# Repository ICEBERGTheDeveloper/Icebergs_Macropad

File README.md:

# Icebergs' Macropad
This is the repo for my first macropad creation!

My macropad has 9 keyboard switches in a matrix, an OLED screen and a Rotary encoder! I will use it for video editing, gaming, and just other usefull things on my computer!
## CAD Model
The whole macropad fits together with just 4 screws on the case.

## Case
I designed this to just hold the PCB with no extra screws. I made 2 support columns underneath the PCB to hold it up at the right height, and it should fit snug with not much wiggle room.
Once I get the parts in real life, I can make the case better as I do not know the actual dimentions for the OLED screen.

## PCB
The PCB was designed with 9 switches, 9 diodes, the Seeed Studio XIAO RP2040, an EC11 Rotary encoder, a 128x32 OLED screen, and a nice silkscreen graphic! The mounting holes in it are for the future if I need to mount the PCB inside the case, but for now, I wont be using them :)

## The Schematic

## Software
The software was made with KMK.
I have most of the code complete, just need to change the buttons and OLED screen
- Currently the switches are just mapped to normal characters, when I get the macropad I will start thinking of what to map them to
### Here are some features I included:
- 3 keyboard layers (1 default, 1 gaming and 1 video editing) - As i said earlier, I only have them mapped to characters currently
- Encoder to switch the layer (double click encoder to enter 'layer switching mode' and then turn encoder clockwise to go to next layer, counter clockwise to go to previous layer, and click the encoder again to confirm)
- OLED screen - This currently only has some text... I will be editing this a lot when my macropad arrives
The software was probably my favourite part of making this macropad (along with PCB design)

## BOM
Finaly, all the parts I used.
- 9x Through-hole 1N4148 Diodes
- 9x MX-Style switches
- 1x EC11 Rotary encoder
- 1x 0.91 inch OLED display
- 9x Blank DSA keycaps
- 4x M3x16mm screws
- And I am *pretty* sure that the heatset inserts are needed... Please tell me? If they are: 4x M3x5mx4mm heatset inserts

#### I do not need the 3D printed case - I have a 3D printer at home

Thank you HackClub for giving us this awesome experience!

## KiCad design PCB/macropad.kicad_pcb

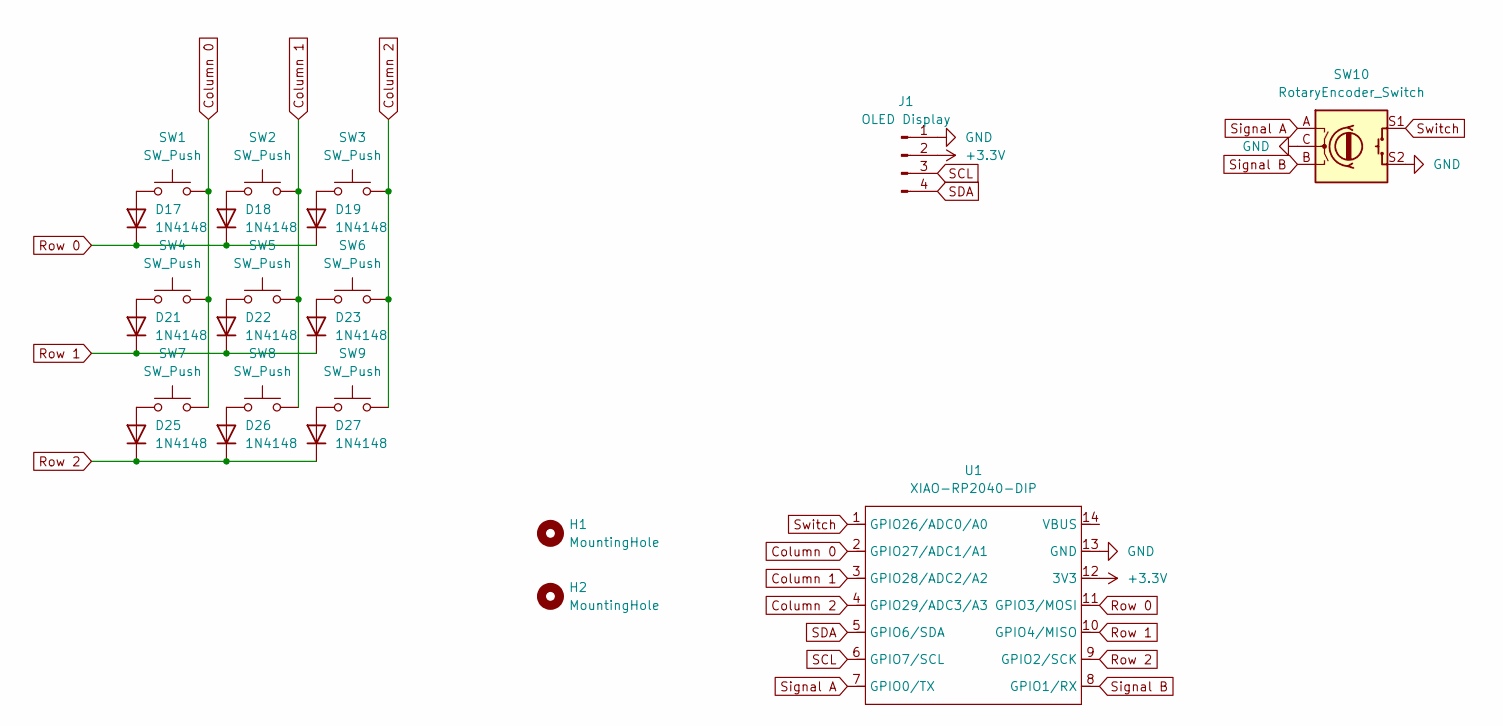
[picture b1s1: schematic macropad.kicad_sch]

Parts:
D17, D18, D19, D21, D22, D23, D25, D26, D27: 1N4148; D_DO-35_SOD27_P7.62mm_Horizontal
H1, H2: MountingHole; MountingHole_3.2mm_M3
J1: OLED Display; SSD1306-0.91-OLED-4pin-128x32
SW1, SW2, SW3, SW4, SW5, SW6, SW7, SW8, SW9: SW_Push; SW_Cherry_MX_1.00u_PCB
SW10: RotaryEncoder_Switch; RotaryEncoder_Alps_EC11E-Switch_Vertical_H20mm
U1: XIAO-RP2040-DIP

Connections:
+3.3V: J1.2, U1.12 (3V3)
Column 0: SW1.2, SW4.2, SW7.2, U1.2 (GPIO27/ADC1/A1)
Column 1: SW2.2, SW5.2, SW8.2, U1.3 (GPIO28/ADC2/A2)
Column 2: SW3.2, SW6.2, SW9.2, U1.4 (GPIO29/ADC3/A3)
GND: J1.1, SW10.C, SW10.S2, U1.13 (GND)
unnamed: D17.2 (A), SW1.1
unnamed: D18.2 (A), SW2.1
unnamed: D19.2 (A), SW3.1
unnamed: D21.2 (A), SW4.1
unnamed: D22.2 (A), SW5.1
unnamed: D23.2 (A), SW6.1
unnamed: D25.2 (A), SW7.1
unnamed: D26.2 (A), SW8.1
unnamed: D27.2 (A), SW9.1
Row 0: D17.1 (K), D18.1 (K), D19.1 (K), U1.11 (GPIO3/MOSI)
Row 1: D21.1 (K), D22.1 (K), D23.1 (K), U1.10 (GPIO4/MISO)
Row 2: D25.1 (K), D26.1 (K), D27.1 (K), U1.9 (GPIO2/SCK)
SCL: J1.3, U1.6 (GPIO7/SCL)
SDA: J1.4, U1.5 (GPIO6/SDA)
Signal A: SW10.A, U1.7 (GPIO0/TX)
Signal B: SW10.B, U1.8 (GPIO1/RX)
Switch: SW10.S1, U1.1 (GPIO26/ADC0/A0)

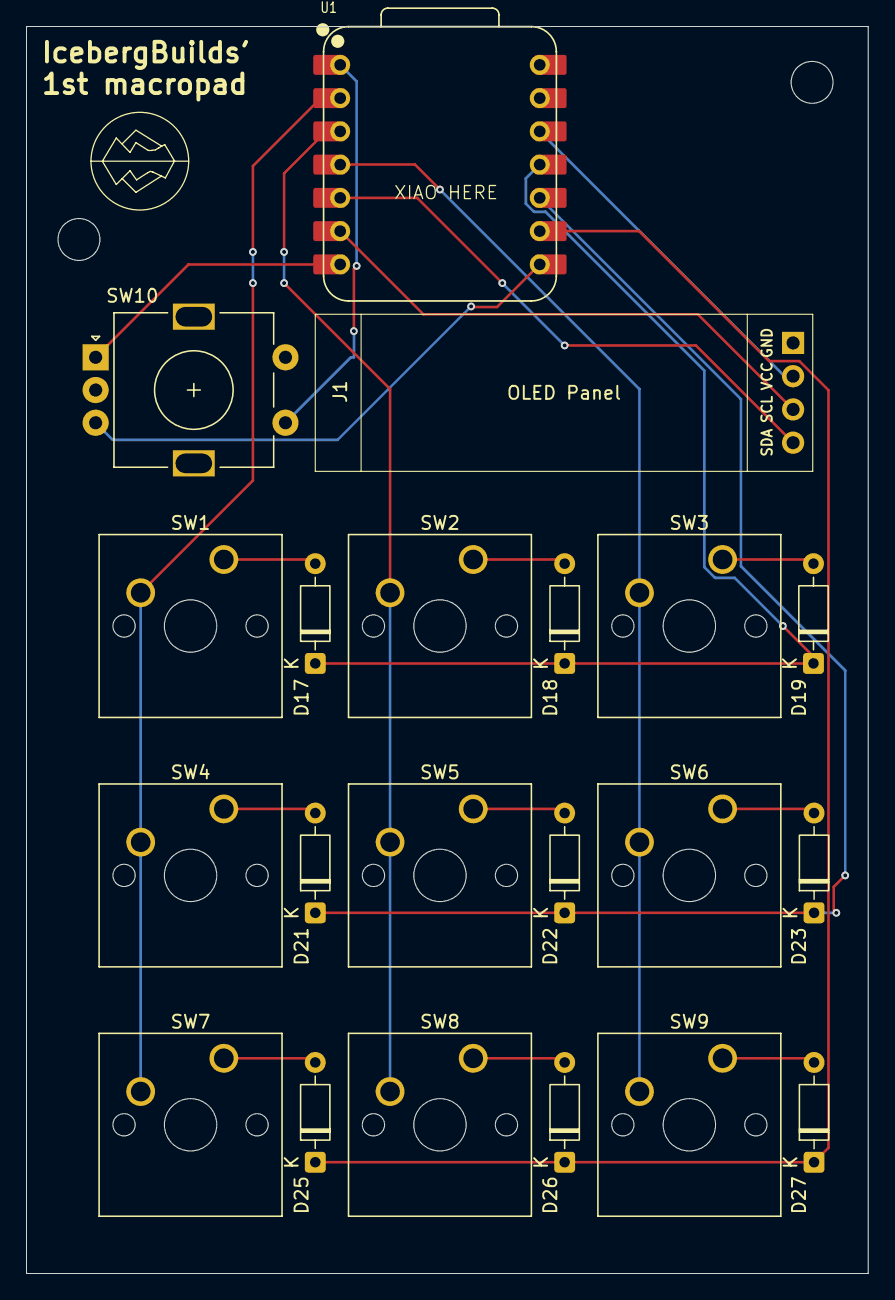
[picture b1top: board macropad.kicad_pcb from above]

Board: 2 copper layers, 64.3 x 95.2 mm, 23 parts (0 on the bottom side), 22 nets.

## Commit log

2026-01-17 Complete README
    Expanded the README to include detailed sections on the case design, PCB components, schematic, software features, and bill of materials.
2026-01-17 Update README.md
    Changed 1 word lol
2026-01-18 Add all macropad files
